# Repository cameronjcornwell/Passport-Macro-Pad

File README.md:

# Credit-Card-Macro-Pad
An upgraded version of the "Debit Card" macro pad.

Keep in mind this isn't anywhere near complete, and that this is also being designed by someone with little to no electrical engineering experience.

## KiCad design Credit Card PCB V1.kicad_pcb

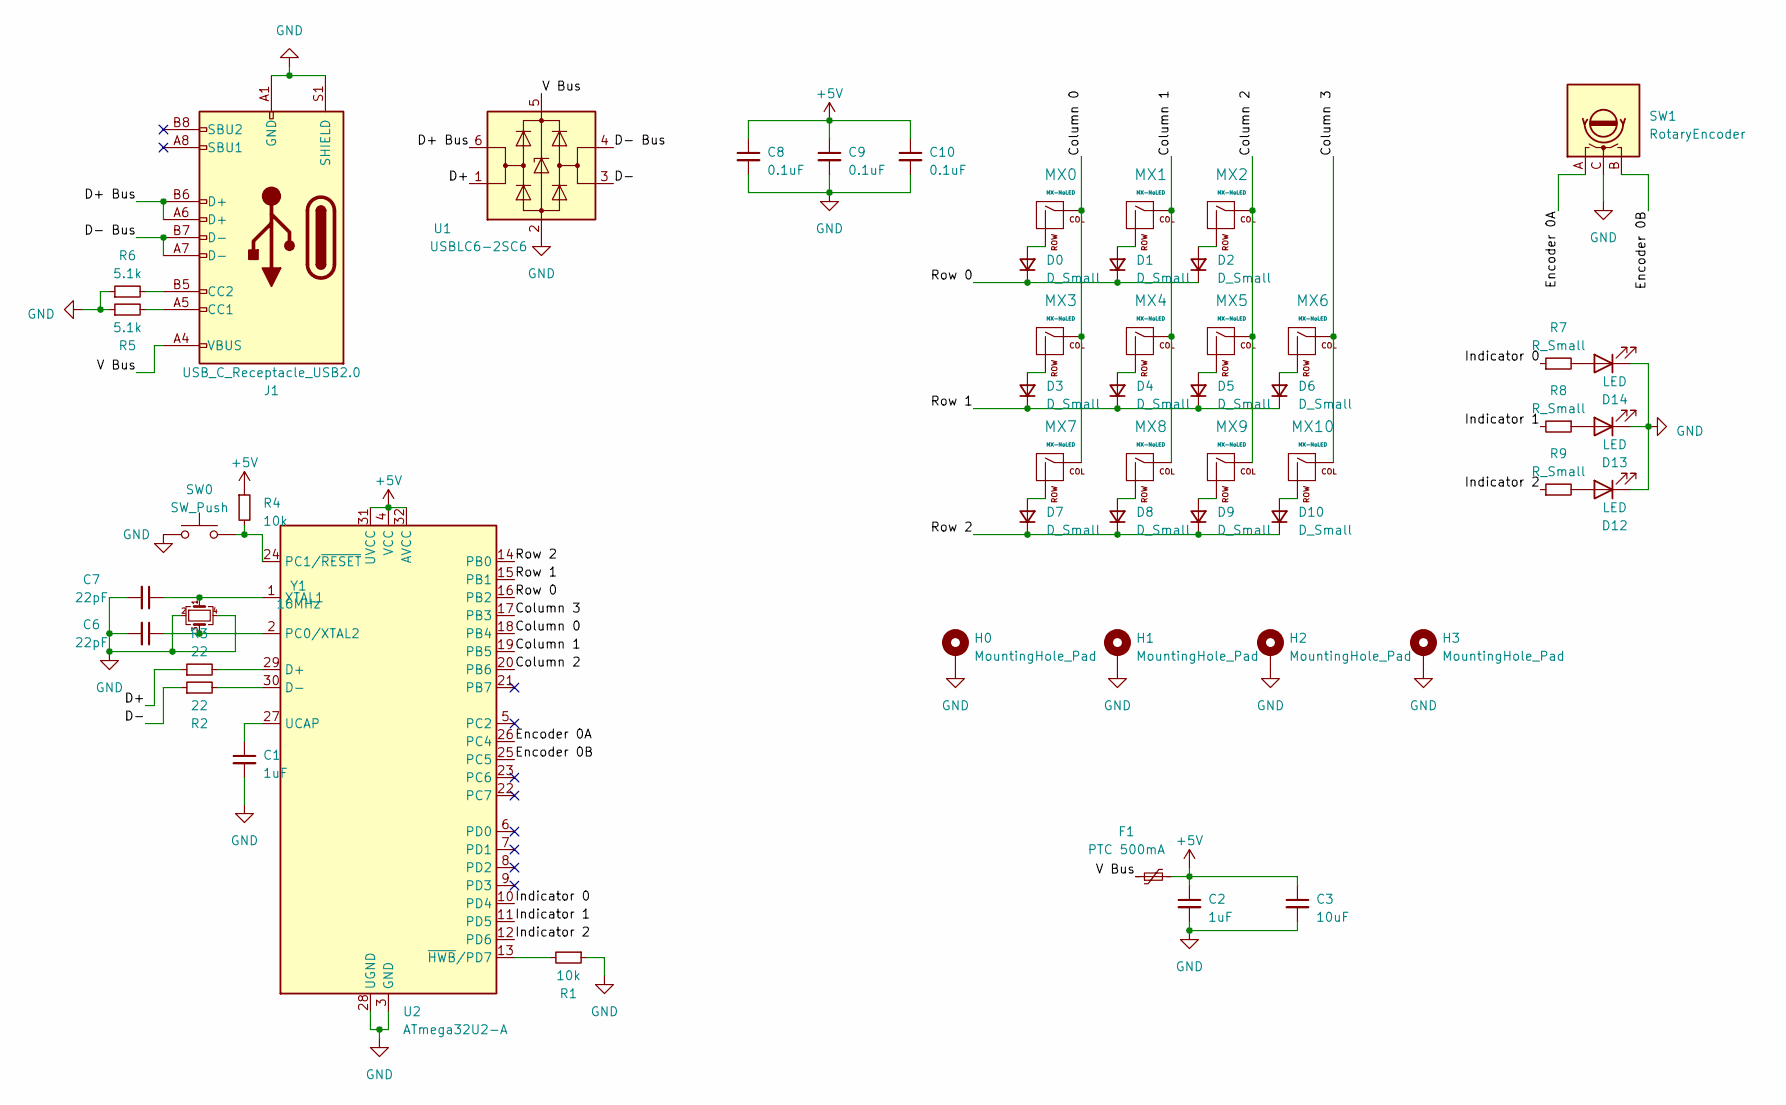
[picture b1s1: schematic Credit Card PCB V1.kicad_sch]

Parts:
C1, C2: 1uF; C_0603_1608Metric
C3: 10uF; C_0603_1608Metric
C6, C7: 22pF; C_0603_1608Metric
C8, C9, C10: 0.1uF; C_0603_1608Metric
D0, D1, D2, D3, D4, D5, D6, D7, D8, D9, D10: D_Small; D_0603_1608Metric
D12, D13, D14: LED; LED_0805_2012Metric
F1: PTC 500mA; Fuse_1206_3216Metric
H0, H1, H2, H3: MountingHole_Pad; MountingHole_2.2mm_M2_Pad_Via
J1: USB_C_Receptacle_USB2.0; GCT_USB4110-GF-A_REVB
MX0, MX1, MX2, MX3, MX4, MX5, MX6, MX7, MX8, MX9, MX10: MX-NoLED; Kailh_socket_PG1350_Revised
R1, R4: 10k; R_0603_1608Metric
R2, R3: 22; R_0603_1608Metric
R5, R6: 5.1k; R_0603_1608Metric
R7, R8, R9: R_Small; R_0603_1608Metric
SW0: SW_Push; SW_SPST_SKQG_WithStem
SW1: RotaryEncoder; RotaryEncoder_Alps_EC12E_Vertical_H20mm
U1: USBLC6-2SC6; SOT-23-6
U2: ATmega32U2-A; TQFP-32_7x7mm_P0.8mm
Y1: 16MHz; Crystal_SMD_Abracon_ABM8G-4Pin_3.2x2.5mm

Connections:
+5V: C2.1, C3.1, C8.1, C9.1, C10.1, F1.2, R4.1, U2.4 (VCC), U2.31 (UVCC), U2.32 (AVCC)
/Column 0: MX0.1 (COL), MX3.1 (COL), MX7.1 (COL), U2.18 (PB4)
/Column 1: MX1.1 (COL), MX4.1 (COL), MX8.1 (COL), U2.19 (PB5)
/Column 2: MX2.1 (COL), MX5.1 (COL), MX9.1 (COL), U2.20 (PB6)
/Column 3: MX6.1 (COL), MX10.1 (COL), U2.17 (PB3)
/D+: R3.1, U1.1 (I/O1)
/D+ Bus: J1.A6 (D+), J1.B6 (D+), U1.6 (I/O1)
/D-: R2.1, U1.3 (I/O2)
/D- Bus: J1.A7 (D-), J1.B7 (D-), U1.4 (I/O2)
/Encoder 0A: SW1.A, U2.26 (PC4)
/Encoder 0B: SW1.B, U2.25 (PC5)
/Indicator 0: R7.1, U2.10 (PD4)
/Indicator 1: R8.2, U2.11 (PD5)
/Indicator 2: R9.1, U2.12 (PD6)
/Row 0: D0.1 (K), D1.1 (K), D2.1 (K), U2.16 (PB2)
/Row 1: D3.1 (K), D4.1 (K), D5.1 (K), D6.1 (K), U2.15 (PB1)
/Row 2: D7.1 (K), D8.1 (K), D9.1 (K), D10.1 (K), U2.14 (PB0)
/V Bus: F1.1, J1.A4 (VBUS), J1.A9 (VBUS), J1.B4 (VBUS), J1.B9 (VBUS), U1.5 (VBUS)
GND: C1.2, C2.2, C3.2, C6.2, C7.2, C8.2, C9.2, C10.2, D12.1 (K), D13.1 (K), D14.1 (K), H0.1, H1.1, H2.1, H3.1, J1.A1 (GND), J1.A12 (GND), J1.B1 (GND), J1.B12 (GND), J1.S1 (SHIELD), R1.1, R5.1, R6.1, SW0.1, SW1.C, U1.2 (GND), U2.3 (GND), U2.28 (UGND), Y1.2, Y1.4
unnamed: D0.2 (A), MX0.2 (ROW)
unnamed: D1.2 (A), MX1.2 (ROW)
unnamed: D2.2 (A), MX2.2 (ROW)
unnamed: D3.2 (A), MX3.2 (ROW)
unnamed: D4.2 (A), MX4.2 (ROW)
unnamed: D5.2 (A), MX5.2 (ROW)
unnamed: D6.2 (A), MX6.2 (ROW)
unnamed: D7.2 (A), MX7.2 (ROW)
unnamed: D8.2 (A), MX8.2 (ROW)
unnamed: D9.2 (A), MX9.2 (ROW)
unnamed: D10.2 (A), MX10.2 (ROW)
unnamed: D12.2 (A), R9.2
unnamed: D13.2 (A), R8.1
unnamed: D14.2 (A), R7.2
unnamed: J1.A5 (CC1), R5.2
unnamed: J1.B5 (CC2), R6.2
unnamed: R3.2, U2.29 (D+)
unnamed: R2.2, U2.30 (D-)
unnamed: C6.1, U2.2 (PC0/XTAL2), Y1.3
unnamed: R4.2, SW0.2, U2.24 (PC1/~RESET)
unnamed: C1.1, U2.27 (UCAP)
unnamed: C7.1, U2.1 (XTAL1), Y1.1
unnamed: R1.2, U2.13 (~HWB/PD7)

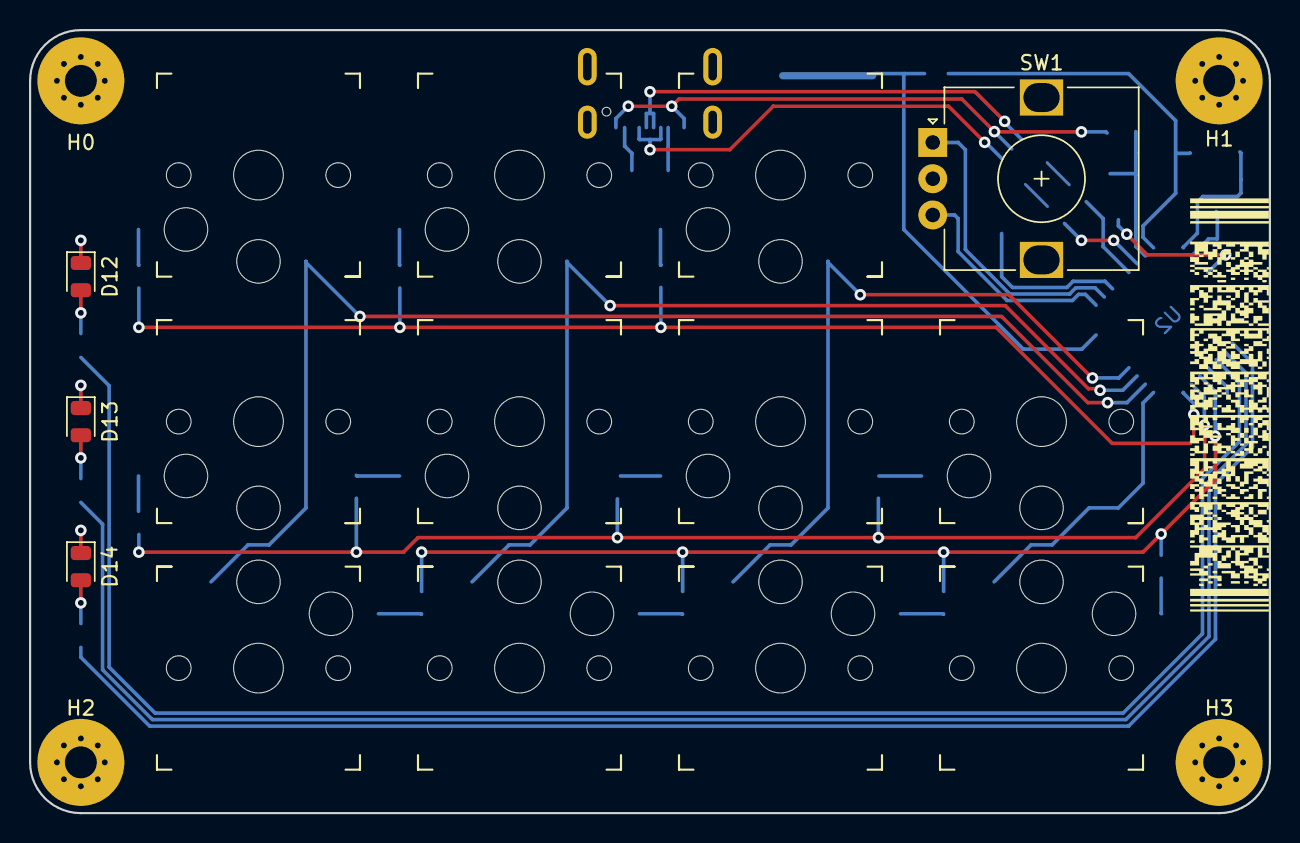
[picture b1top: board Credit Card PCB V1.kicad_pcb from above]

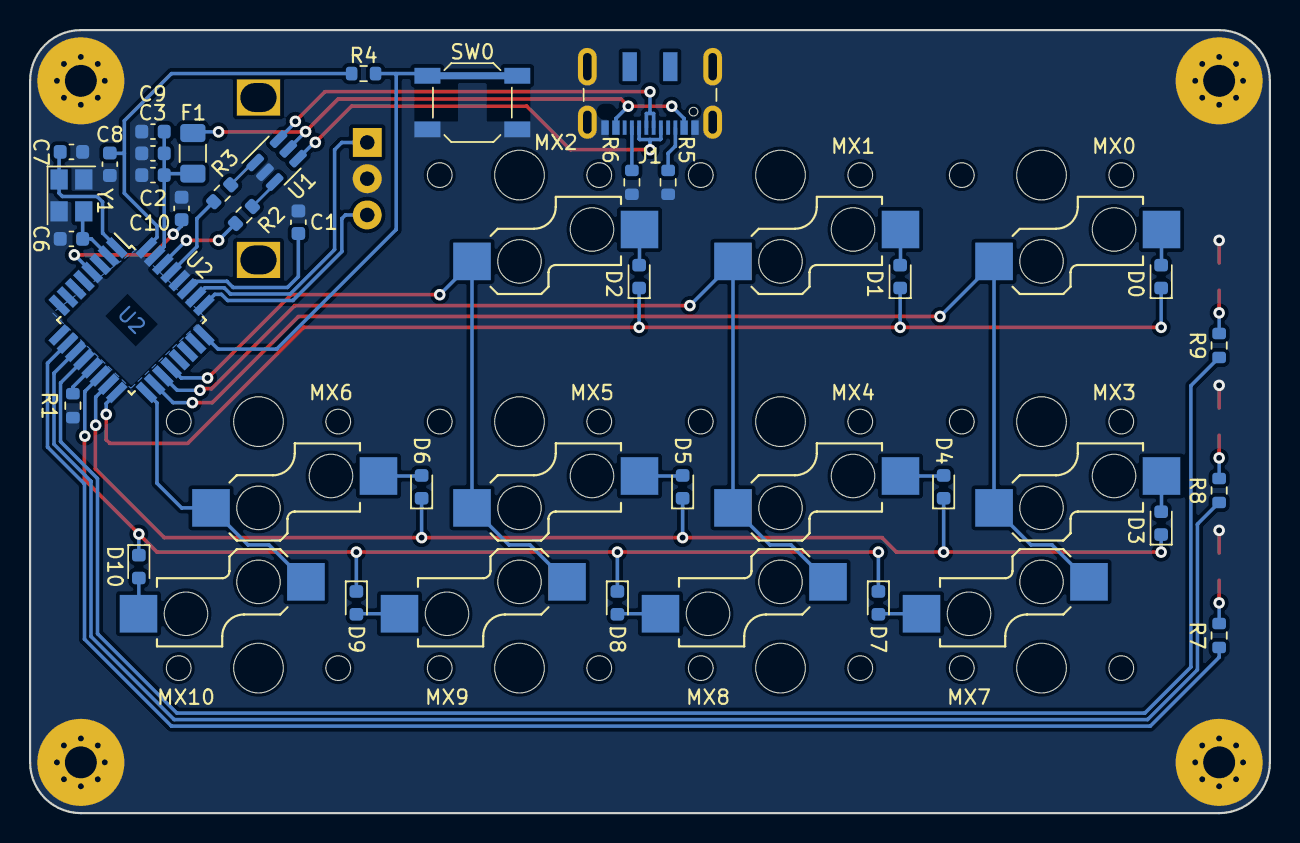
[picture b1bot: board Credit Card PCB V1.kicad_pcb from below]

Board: 2 copper layers, 85.5 x 54.0 mm, 53 parts (34 on the bottom side), 42 nets.

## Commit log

2023-02-28 Initialize Project
2023-02-28 Update to Schematic
2023-03-13 Uhhhhhh fuckin uhhhhhhh probably an update or something idk
2023-03-15 Large Update
2023-03-20 Chunky Update
2023-03-24 Another Chunky Update
2023-03-24 STUFF
2023-03-26 USB C Receptacle Change
    Changed the usb c receptacle to a japanese standard one. I'm too lazy to go back and look up what it is.
2023-03-31 Just a couple small things
2023-04-02 Adding slikscreen logo
